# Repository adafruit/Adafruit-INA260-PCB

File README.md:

## Adafruit INA260 High or Low Side Current and Power Sensor PCB

<a href="http://www.adafruit.com/products/4226"><br/>
Click here to purchase one from the Adafruit shop</a>

PCB files for the Adafruit INA260 High or Low Side Current and Power Sensor. 

Format is EagleCAD schematic and board layout
* https://www.adafruit.com/product/4226

### Description

This breakout board may well be the last current sensing solution you every need to buy. Not only can it do the work of two multimeters, but it can do it with amazing precision and flexibility. With it you can measure high or low side DC current, the bus voltage, and have it automatically calculate the power. It can do so over impressive voltage, current, and temperature ranges with better than 1% accuracy, all while delivering the data in an easy to use format over I2C.

Works great with any microcontroller that is CircuitPython or Arduino compatible as well as single board computers such as the Raspberry Pi. It is compatible with 3V or 5V logic and can measure bus voltages up to **+36VDC. Not for use with AC voltages**.

Most current-measuring devices operate with some notable constraints that limit what they can be used for. Many are low-side only which can cause issues as the ground reference changes with current. Others like its little sister the INA219B avoid this by measuring on the high side but need to change their shunt resistor to measure different current ranges. The INA260 avoids these limitations, and with it's integrated precision shunt resistor it can be used to measure as much as **+36V** at up to **15A Continuous** on either the _high or low side_. Wow!

The voltage across the integrated 2 milliohm (.002 ohms!), 0.1% shunt resistor is measured by the internal 16 bit ADC, allowing for measurements over the impressive current range with a resolution of 1.5 mA. (The resistance of the resistor is so low that some multimeters will register it as a short!)

In a high side configuration the bus voltage measurement and power calculation can be retrieved accurately, however advanced hackers wanting to measure bus voltage in a low side configuration will need to cut the jumper connecting **V+** to **VBUS** and connect the **VBUS** pin to the voltage bus.

Comes as a fully assembled breakout board with a 5.08mm terminal block (extra chunky!) and header. Some light soldering is required to attach the header and terminal block.

### License

Adafruit invests time and resources providing this open source design, please support Adafruit and open-source hardware by purchasing products from [Adafruit](https://www.adafruit.com)!

Designed by Bryan Siepert for Adafruit Industries.

Creative Commons Attribution/Share-Alike, all text above must be included in any redistribution. 
See license.txt for additional details.

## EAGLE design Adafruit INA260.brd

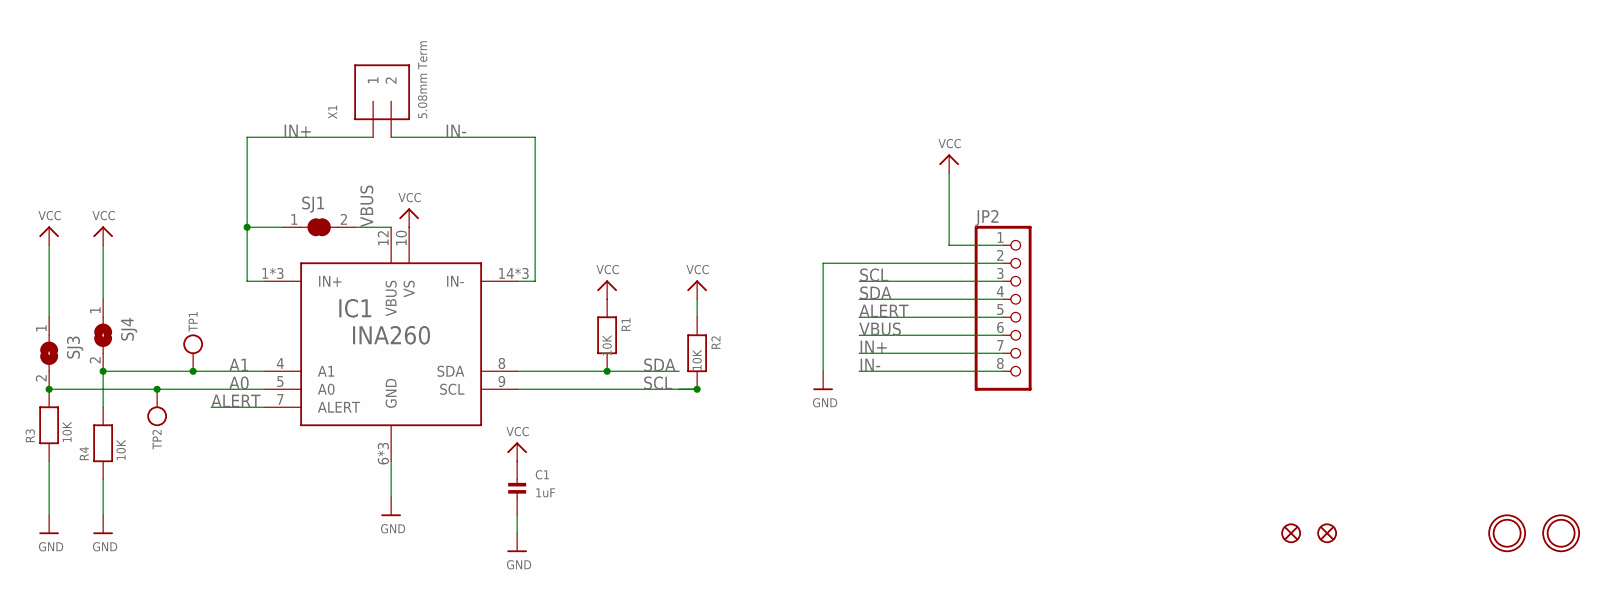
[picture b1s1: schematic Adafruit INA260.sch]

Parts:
C1: 1uF; 0603-NO
FID3, FID4: MICROBUILDER_FIDUCIAL""; MICROBUILDER_FIDUCIAL_1MM
IC1: INA260; TSSOP16
JP2: HEADER-1X870MIL; 1X08_ROUND_70
R1, R2, R3, R4: 10K; 0603-NO
SJ1: SOLDERJUMPER_CLOSED; SOLDERJUMPER_CLOSEDWIRE
SJ3, SJ4: SOLDERJUMPER; SOLDERJUMPER_ARROW_NOPASTE
TP1, TP2: TESTPOINTROUND1.5MM; TESTPOINT_ROUND_1.5MM
U$7, U$8: MOUNTINGHOLE2.5; MOUNTINGHOLE_2.5_PLATED
X1: 5.08mm Term; TERMBLOCK_508_1X2

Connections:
A0: IC1.5 (A0), R3.2, SJ3.2, TP2.P$1
A1: IC1.4 (A1), R4.2, SJ4.2, TP1.P$1
ALERT: IC1.7 (ALERT), JP2.5
GND: C1.2, IC1.6 (GND), IC1.11 (GND), IC1.13 (GND), JP2.2, R3.1, R4.1
IN+: IC1.1 (IN+), IC1.2 (IN+), IC1.3 (IN+), JP2.7, SJ1.1, X1.P$3 (1)
IN-: IC1.14 (IN-), IC1.15 (IN-), IC1.16 (IN-), JP2.8, X1.P$4 (2)
SCL: IC1.9 (SCL), JP2.3, R2.2
SDA: IC1.8 (SDA), JP2.4, R1.2
VBUS: IC1.12 (VBUS), JP2.6, SJ1.2
VCC: C1.1, IC1.10 (VS), JP2.1, R1.1, R2.1, SJ3.1, SJ4.1

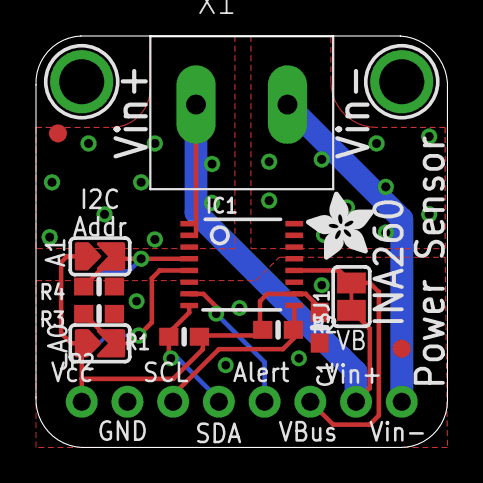
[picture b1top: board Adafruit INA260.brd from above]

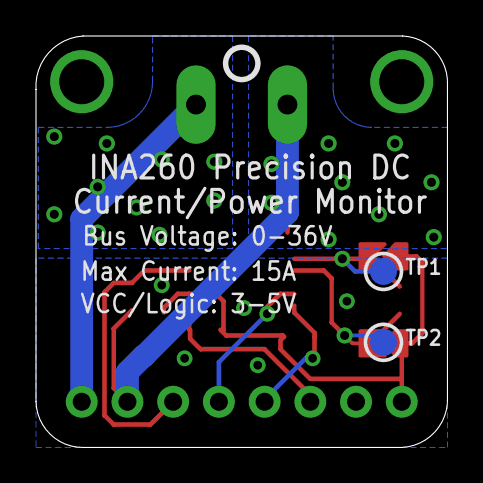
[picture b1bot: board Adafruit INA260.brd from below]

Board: 2 copper layers, 22.9 x 22.9 mm, 19 parts (3 on the bottom side), 10 nets.

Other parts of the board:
U$1: ADAFRUIT_3.5MM
U$6: PCBFEAT-REV-040

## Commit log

2019-05-01 Adding brd/sch files
2019-07-17 updated to use cookiecutter for pcb repos
2019-07-17 added missing copy

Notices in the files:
parts and their libraries:
microbuilder: This work is placed in the public domain, and may be freely used for commercial and non-commercial work with the following conditions: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
